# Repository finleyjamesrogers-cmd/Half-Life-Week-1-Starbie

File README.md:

# Starbie Adaptation
Starbie is a tiny motion-controlled digital pet with minimal gameplay buttons. Instead of pressing buttons, you interact with it by physically moving the board.

## What is it?
The Starbie is designed to be your own personal digital pet that can show its personality through a small display, react to the way you handle it and give real time responses and feedback.

The board includes a microcontroller, display, gyro/motion sensor and Temperature/Humidity Sensor all in a compact PCB design.

It is powered by USB and made for beginner-friendly through-hole soldering for the add on components

## Why?
This project was created to complete week 1 of half life 2026

## Highlights
- Temperature and Humidity sensors to get real time info
- Gyro based selector to make it more interactive without the need to add more buttons
- Customisable beginner section of Arduino code for easy ways to make it harder/easier to keep your pet happy
- Small display for real time feedback and visual selection/prompts

## Visual Features
- Tilt control selection.
- Sparkles that follow the pet.
- Visual indicators of sleep/love in the form of Zz's and Hearts.
- Pet explores around when not being instrusted.
- Little shake to acknowledge instruction.
- Lots more, look through the code or build it to find out!  

## Project Status
The PCB design as well as the Arduino starter firmware are included, the default program is a turtle pet with a tilt-controlled radial menu, hidden stats, and a range of reactions going from dancing to eating to sleeping.

## What was used to make it?
The original tutorial Starbie, by SharKingStudios was used to guide most of the design with extra input from myself for the creative design features including the pet sprite.

- KiCad was used for the PCB schematics, design and routing.

- Arduino was used for the firmware.

- Piskel was used for creating the turtle sprite.

### Link to the BOM (its also in the side pannel)
https://github.com/finleyjamesrogers-cmd/Half-Life-Week-1-Starbie/blob/0c3692dca871a0263f27b8f05468195b88a70d30/BOM.csv

### Eye Candy for anyone who wants it!

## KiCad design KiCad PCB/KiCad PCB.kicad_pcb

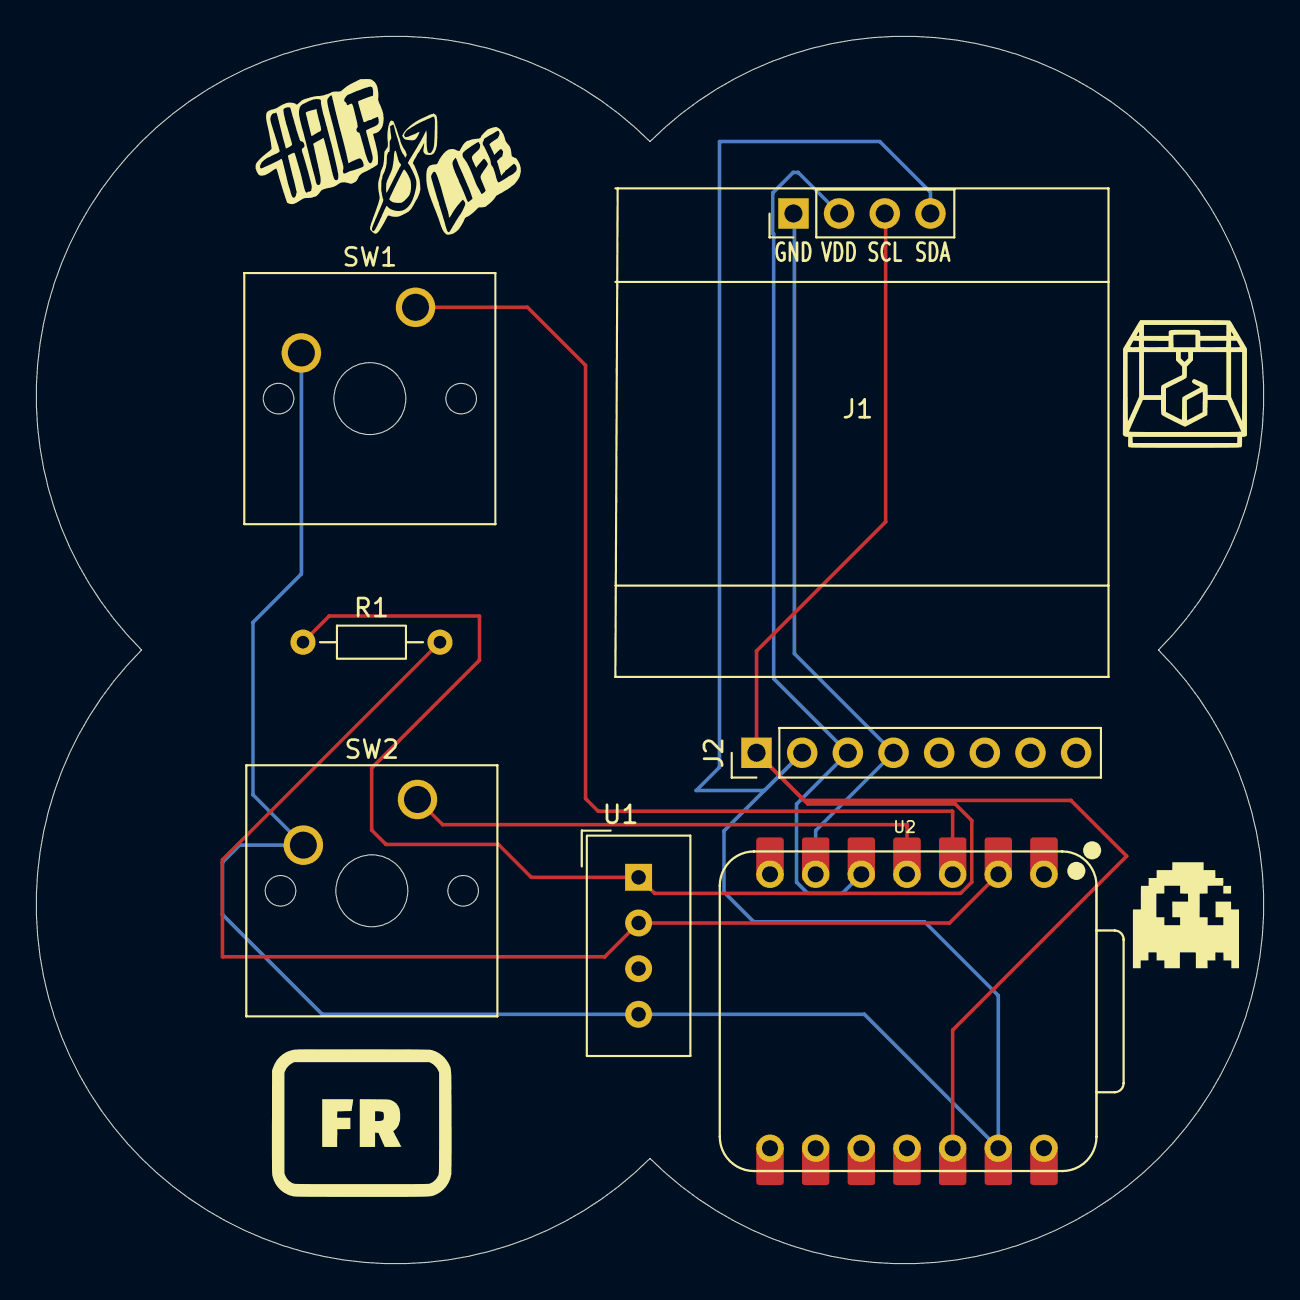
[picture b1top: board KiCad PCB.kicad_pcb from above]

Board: 2 copper layers, 68.3 x 68.3 mm, 7 parts (0 on the bottom side), 7 nets.

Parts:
J1: Conn_01x04_Pin; Display_128x64_096_I2C
J2: Conn_01x08_Pin; PinHeader_1x08_P2.54mm_Vertical
R1: R; R_Axial_DIN0204_L3.6mm_D1.6mm_P7.62mm_Horizontal
SW1, SW2: SW_Push; SW_Cherry_MX_1.00u_PCB
U1: DHT11; Aosong_DHT11_5.5x12.0_P2.54mm
U2: XIAO-ESP32-C3-SMD; XIAO-ESP32-C6-DIP

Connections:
+3.3V: J1.3, J2.1, R1.1, U1.1 (VDD), U2.12 (3V3_OUT)
/DHT11 DATA: R1.2, U1.2 (DATA), U2.2 (D1)
/GPIO2: SW1.1, U2.3 (D2)
/GPIO3: SW2.1, U2.4 (D3)
/SCL: J1.2, J2.3, U2.5 (D4)
/SDA: J1.1, J2.4, U2.6 (D5)
GND: J1.4, J2.2, SW1.2, SW2.2, U1.4 (GND), U2.13 (GND)
